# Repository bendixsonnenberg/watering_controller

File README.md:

# Watering Controller
A tinkering project to automate watering plants in a greenhouse and analyzing data afterwards.  
Current Progress can be seen in "Status" at the bottom.

Codewise: an exploration of using embedded rust, specificaly [embassy](https://embassy.dev/).

## Short Overview
### Hardware
Per pot:
  - 1 STM32F103C8# 
  - capacitive moisture sensor
  - valve
  - mcp2551 can RX/TX
  - Mosfet IRFB3006 (there are alternatives, this one worked for us)

Central Controller:
  - Pico 2 W (pico 1 2 would be enough)
  - 2x16 LCD Display
  - MCP2515 for can communication.
  - UX to be determined

Additional Hardware needed:
  - Some kind of reservoir
  - Silicone tubes for delivering water to valves

### System Design
The central controller communicates with each moisture sensor over CAN-Bus.
The Specs for this Communication can be found [here](/can_protocol.md). The implementation is found [here](/can_protocol).
The moisture sensors get a threshold and use their valves to hold that threshold, currently through a simple comparision (potential PID).

## Current Status
August '25: Web-functions added, central controller accesses WLAN. Sensorreadings possible through network with webinterface-prototype.

## Story and some Context
After building a greenhouse on our little roof terrace for my fiancée, I stumbled upon the biggest problem in the private greenhouse industry. While tomatoes and cucumbers thrived, the biggest recurring problem was watering the plants, as you have to do so every day; on hot days, multiple times a day.
The solution was obvious: I turned to my good friend Bendix and we started engineering the hell out of this seemingly small problem. The idea got bigger and bigger, until we suddenly had the first prototype running on a cheap patch panel. Our system was actually
reading live moisture data and maintaining a moisture level for several days. The next step was soldering prototype v2, which is currently running in the greenhouse.  
Throughout the process, I had lots of ideas for little extras, such as a menu operated through a rotary encoder on an LCD display or RGB LEDs. Because everything is better with RGB. The final version is supposed to support up to 256 pots (far too many for the 2 x 1.2m²), so the system is adaptable for larger greenhouses. We are planning to implement a
web interface and push notifications to smartphones, so even while being abroad, there is no need for close monitoring by a third party. But these are future dreams. Our current priority is the watering and monitoring functionality – all while the CAN network does its job.  
Bendix has been documenting his progress in code here since day one. I joined GitHub mainly to be a part of it. To be honest: I have absolutely no clue about coding other than basic principles and a rough idea of what computers can do. My main background is being a mechanic by trade. Now I do my part by
trying to document our progress and give a little context about what we do.
I'll try to update regularly – who knows, this might one day attract public interest.  

Small Addition: I startet building a webinterface, all while learning how to work with HTML and JavaScript. If you're interested, click [here](https://github.com/DoktorWussow/gewachshausomatwebinterface).

-Philipp
## Milestones
June '25: working menu on LCD-Display with individual IDs and live data, navigation possible through rotary encoder and "return"-button  
June '25: data saved, showing 9 day continuous watering without crashes or similar issues; moisture level plausible  
July '25: Hardware for easier refilling added, also new water container  
July '25: Webinterface concept working, reference [here](https://github.com/DoktorWussow/gewachshausomatwebinterface).  
August '25: Access to live data possible through Webinterface concept.
## Status History
Up to July '25: Two pot-sensors together with central controller, currently set up in greenhouse, with CAN-Network and watering function working as far as assessable. Menu working, displayed on LCD.  
Up to August '25: Three pot-sensors together with central controller, currently set up in greenhouse, with CAN-Network and watering function working fairly reliable. Menu working, displayed on LCD. RGB-LEDs added for easier identification while changing thresholds. Humidity/Temperaturesensor added. All data is logged on SD-Card.

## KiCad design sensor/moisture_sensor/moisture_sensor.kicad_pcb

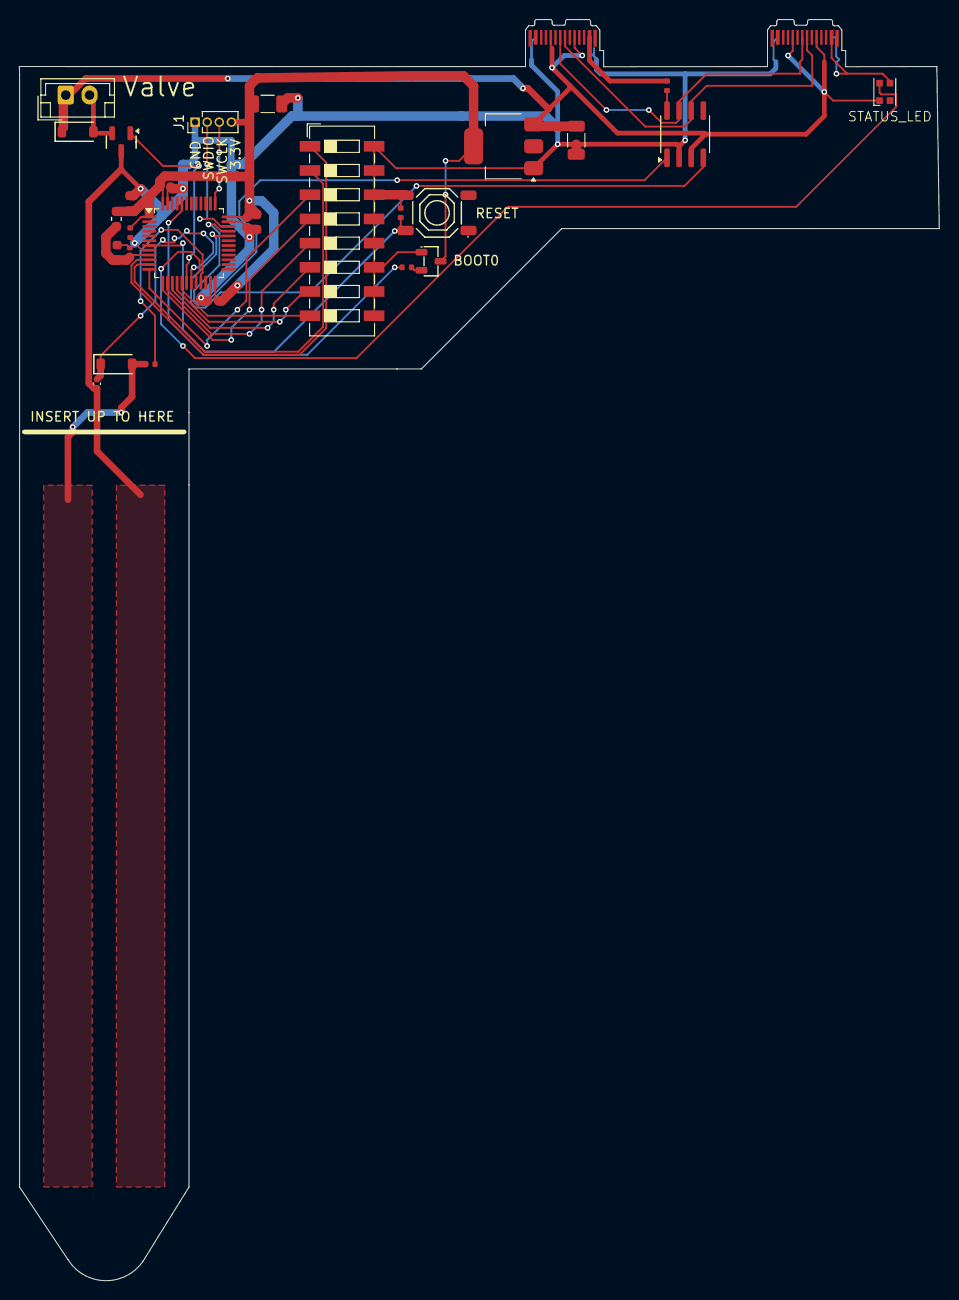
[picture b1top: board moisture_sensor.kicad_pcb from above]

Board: 2 copper layers, 96.5 x 132.3 mm, 30 parts (0 on the bottom side), 30 nets.

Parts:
C1, C2, C3, C5, C6, C9: 100n; C_0402
C4: 10u; C_0603
C7, C8: 1u; C_0603
C10, C11: 22u; C_1206_3216Metric
C14: 100n; C_0402_1005Metric
D1, D2: 1N4148W; D_SOD-123
D3: WS2812B; LED_WS2812B-2020_PLCC4_2.0x2.0mm
FB1: 120R; L_0603
J1: Conn_01x04_Socket; PinHeader_1x04_P1.27mm_Vertical
J2: Conn_01x02_Pin; JST_EH_B2B-EH-A_1x02_P2.50mm_Vertical
P1, P2: USB_C_Plug_USB2.0; USB_C_Plug_JAE_DX07P024AJ1
Q1: AO3400A; Q_SOT-23
R1, R2, R3: 10k; R_0402
S1: Tactile Button, 160gf; SW-SMD_4P-L5.1-W5.1-P3.70-LS6.5-TL-2
SW2: SW_SPDT; SOT-23-3_L2.9-W1.3-P0.95-LS2.4-BR
SW3: SW_DIP_x08; SW_DIP_SPSTx08_Slide_6.7x21.88mm_W6.73mm_P2.54mm_LowProfile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
U1: STM32F103C8Tx; LQFP-48_7x7mm_P0.5mm
U2: MCP2551-I-SN; SOIC-8_3.9x4.9mm_P1.27mm
U3: AMS1117-3.3; SOT-223-3_TabPin2

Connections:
+3.3V: C1.1, C2.1, C3.1, C4.1, C5.1, C8.1, C10.1, FB1.2, J1.4, SW2.3 (C), U1.1 (VBAT), U1.24 (VDD), U1.36 (VDD), U1.48 (VDD), U3.2 (VO)
+3.3VA: C6.1, C7.1, FB1.1, U1.9 (VDDA)
/ADC12_IN9: C14.1, D1.1 (K), U1.19 (PB1)
/BOOT0: R1.2, U1.44 (BOOT0)
/CANH: P1.A6 (D+), P2.A6 (D+), U2.7 (CANH)
/CANL: P1.A7 (D-), P2.A7 (D-), U2.6 (CANL)
/CAN_RX: U1.32 (PA11), U2.4 (RXD)
/CAN_TX: U1.33 (PA12), U2.1 (TXD)
/NRST: C9.1, S1.2 (B), U1.7 (NRST)
/SWCLK: J1.3, U1.37 (PA14)
/SWDIO: J1.2, U1.34 (PA13)
/SW_BOOT0: R1.1, SW2.2 (B)
/TIM2_CH3: R3.2, U1.21 (PB10)
GND: C1.2, C2.2, C3.2, C4.2, C5.2, C6.2, C7.2, C8.2, C9.2, C10.2, C11.2, C14.2, D3.3 (VSS), J1.1, P1.A1 (GND), P1.A12 (GND), P1.B1 (GND), P1.B12 (GND), P1.S1 (SHIELD), P2.A1 (GND), P2.A12 (GND), P2.B1 (GND), P2.B12 (GND), P2.S1 (SHIELD), Q1.3 (D), R2.2, S1.4 (D), SW2.1 (A), SW3.9, SW3.10, SW3.11, SW3.12, SW3.13, SW3.14, SW3.15, SW3.16, U1.8 (VSSA), U1.23 (VSS), U1.35 (VSS), U1.47 (VSS), U2.2 (VSS), U3.1 (GND)
unnamed: D2.2 (A), J2.2, Q1.2 (S)
unnamed: D3.4 (DIN), U1.20 (PB2)
unnamed: P1.A5 (CC), P2.A5 (CC)
unnamed: P1.B5 (VCONN), P2.B5 (VCONN)
unnamed: Q1.1 (G), U1.18 (PB0)
unnamed: SW3.1, U1.10 (PA0)
unnamed: SW3.2, U1.11 (PA1)
unnamed: SW3.3, U1.12 (PA2)
unnamed: SW3.4, U1.13 (PA3)
unnamed: SW3.5, U1.14 (PA4)
unnamed: SW3.6, U1.15 (PA5)
unnamed: SW3.7, U1.16 (PA6)
unnamed: SW3.8, U1.17 (PA7)
unnamed: R2.1, U2.8 (Rs)
SOIL_C_PWM: D1.2 (A), R3.1
VBUS: C11.1, D2.1 (K), D3.1 (VDD), J2.1, P1.A4 (VBUS), P1.A9 (VBUS), P1.B4 (VBUS), P1.B9 (VBUS), P2.A4 (VBUS), P2.A9 (VBUS), P2.B4 (VBUS), P2.B9 (VBUS), U2.3 (VDD), U3.3 (VI)

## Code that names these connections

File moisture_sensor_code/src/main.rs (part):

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    valve_control: ValveResources {
        adc: ADC1,
        valve_pin: PC13,
        moisture_pin: PA0,
    },
    can_control: CanResources {
        can: CAN,
        can_rx: PA11,
        can_tx: PA12,
    },
    dev_id: DevIdResources {
        b0: PB11,
        b1: PB10,
        b2: PB1,
        b3: PB0,
        b4: PA7,
        b5: PA6,
        b6: PA5,
        b7: PA4,

    }
    // the led pins and timer have to be together, it is impossible to do something forbidden here, since rustc will not compile
    led_pins: LedResources {
        timer: TIM2,
        red: PA2,
        green: PA1,
        blue: PA3,
    }

    // dht11
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
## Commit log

2025-04-01 init
2025-04-01 remove mut
2025-04-02 add sd card handeling
2025-04-02 rename code folder
    replace if let with iserr
2025-04-02 add plan for can
2025-04-03 add can tester and can protocol
2025-04-03 cargo fix
2025-04-08 update spi sd card
2025-04-09 add more error reporting and make sd card work
2025-04-09 add rp_controller init
2025-04-10 config moisture_sensor
2025-04-11 working blinky and can bus
2025-04-11 working blinky
2025-04-11 removed commented code
2025-04-12 move shared can info to seperate crate
2025-04-13 add adc to rp_controller
2025-04-13 add external clock on water controller
2025-04-14 remove debug outputs
2025-04-14 apply cargo fix
2025-04-14 update can contract and add tests
2025-04-14 add sd card interaction to rp controller
2025-04-14 add backoff time and watering time as commands
2025-04-14 add errorcode
2025-04-16 add pcb layout
2025-04-19 made linear correction function more robust
2025-04-22 drop canafter getting values
    refactor dev id to function
2025-04-23 increase length of line for logging, suspect that this lead to crashes
2025-04-25 add additional logging
2025-04-25 factor out controller id to const; add support for announcment
2025-04-25 add bitmap for sensor tracking
2025-04-28 move can communication to seperate task for rp
    use channels to communicate
    this leads to a better seperation of concerns
2025-04-29 add can bitmap
2025-04-29 add menu crate
2025-05-01 add generics to sensors
2025-05-01 current up to date state of the rp controller software
2025-05-04 change logging for sd card write errors
2025-05-04 can tx now checks if a send buffer is free before sending, receive waits for the receive interrupt
2025-05-05 only try to send a can message if there is room in the tx buffers
2025-05-05 fix losing send_channel messages by not finding a free tx buffer
2025-05-07 send settings to each new sensor when announced
2025-05-19 added README
2025-06-04 add flake
2025-06-04 update gitignore
2025-06-04 remove flake.lock
2025-06-04 add rp controller schematic
2025-06-05 add getting the id from pin inputs
2025-06-05 remove adc
2025-06-05 change menu
    format
2025-06-05 add lcd display and menu buttons
2025-06-06 menu communication with sensors
2025-06-06 working version with one sensor
2025-06-06 delay announcement based on dev_id;
    sd_card for multiple sensors, dynamicly
    announcement delay to avoid clogging the can
2025-06-06 increase backoff time, reverse direction of rotary encoder
2025-06-06 add moisture to sensor window
2025-06-06 fix clippy warnings
2025-06-07 move sd_card stuff to extern file
2025-06-07 refactor menu implementation
2025-06-07 refactor can
2025-06-08 write time to sd card and fix order of moisture and threshold
2025-06-08 Create LICENSE
2025-06-09 fix id getting
2025-06-09 increase announcement time , change defaults
2025-06-09 adjust text
2025-06-09 remove hysterese from can contract
2025-06-10 Update README.md
    dwasw
2025-06-10 Update README.md
    Added Space in last line
2025-06-10 Update README.md
    Some Structure added, mosfet added, headlines for future details prepared
2025-06-10 Update README.md
    Small changes in structure
2025-06-11 Update README.md
    Status update, Order changed, Milestone added
2025-06-12 Update README.md
    Story/Context added
2025-06-13 add ultrasonic sensor readout function
2025-06-13 factor out moisture step size; set it to 10
    resolves #5
2025-06-13 add light to can contract, make data be returned as enum for more information returned in a single file
2025-06-13 implement set light for a sensor
    for #3
2025-06-13 rename Enum
2025-06-13 make the lcd interaction async,
    in case the display is disconnected, this will keep the rest of the device running.
    This will not help with reinitilizing the display so a restart is still required
2025-06-13 create new task for led_control, implement random
    relates to #2
2025-06-13 light up sensor led on focus
    whenever a sensor is selected, their led should shine red
    relates to #2
2025-06-20 add watering time & backoff time to menu crate
    regards #7
2025-06-20 add backoff_time, watering_time to menu
    relevant for #7
    this commit doubles the number of can frames sent for each populate call
    it may be that this leads to the menu interface seeming slower or losing connection more often
    if that is the case, we need to seperate the populate call out into multiple calls depending on the setting that needs to be updated/set
2025-06-20 check if coler values are legal before sending them
2025-06-20 read moisture value during backoff time
2025-06-20 increase sample time to get more stable values
2025-06-22 add units, remove useless spaces #7
2025-06-23 switch direction of scroll in new settings, add flake.lock
2025-06-23 Create Prototypes
2025-06-23 test
2025-06-23 Revert "test"
    This reverts commit dfb4e7e7830218fc99c9b68645c307594ffb26df.
    the commit was mad by mistake
2025-06-23 add remove hardware from gitignore
2025-06-23 prototype v2 schematic
2025-06-23 Update README.md
    Milestone added
2025-06-23 logfiles saved
2025-06-23 add visualization help
2025-06-23 change processing over to python
2025-06-23 add display and processing packages to flake
2025-06-23 use simplet x11 display
2025-06-24 rework can contract
    consolidates the settings into a single command, also does that with the sensor readings
    Implement bitmaps to communicate the availabe sensor or light commands
    add convinence function that produces the embedded_can::Frame directely from CommandData
2025-06-26 stashing
2025-06-27 processed files to gitignore
2025-06-27 add flake; remove from gitignore
2025-06-28 remove useless line
2025-06-28 implement new can api in sensor firmware
2025-06-28 implement the new can_contract api in can.rs for rp_controller
    not quite done yet, still need to fix stuff in other files that interact with this file,
    the function signatures have changed. This was duóne because it will be way cleaner although
    it does need more work in other locations
2025-06-28 implement new can_contract api for rp_controller
    needs to be tested before this can be considered complete
2025-07-04 log files input
2025-07-13 dht 11 added
2025-07-13 add enviromental sensors
2025-07-13 add enviromental sensor to log file
2025-07-13 fix direction of sensor selction
2025-07-13 Update README.md
    Status update
2025-07-13 party mode implemented
2025-07-13 fixed reversed order of backoff and watering time
2025-07-18 update cargo.toml and read ssid and pwd from settings file
2025-07-18 Update README.md
    Reference to Webinterface added.
2025-07-18 add start of net api
2025-07-18 add method and path detection, implement /sensors
2025-07-18 add 404 missing response and error handeling
2025-07-19 add /sensor api
2025-07-19 update flake versions
2025-07-22 update can_protocol description
    since the can protocol was reworked, this documentation was not adapted
2025-07-24 Create excelmakro
2025-07-24 implementing experimental software debounce #18
2025-07-26 get data from http request
2025-07-26 add post sensor endpoint #19
2025-07-26 return ok after setting up sensor
2025-07-26 implement party mode #19,
    refactor the party mode to own module
2025-07-26 add error handeling infastructure #17
2025-07-26 prevent error reporting from locking up
    if we can't log the error, just drop it
2025-07-26 report if sensor is not responding #17
2025-07-26 report booted error
2025-07-26 sub freezing temps for error codes
    include sensor id in error code #17
2025-07-27 include error return in web interface #17 #19
2025-08-18 add information about release mode to moisture sensor
2025-08-26 add webinterface end button debouncing
2025-08-26 Status update
2025-08-28 cleanup unecessary code
2025-08-28 static html serving
2025-08-28 add persistant settings for the sensors
    this will close #1
    it is more difficult than expected to make the rp write the settings back to the sd card, so that will have to wait for now
2026-03-07 update flake-nix
2026-03-08 add rust analyzer
